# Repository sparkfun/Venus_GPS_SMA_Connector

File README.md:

**NOTE:** *This product has been retired from our catalog. If you are looking for more up-to-date info, please check out some of these resources to see how other users are still hacking and improving on this product.*
* *[SparkFun Forum](https://forum.sparkfun.com/)*
* *[Comments Here on GitHub](https://github.com/sparkfun/Venus_GPS_SMA_Connector/issues)*
* *[IRC Channel](https://www.sparkfun.com/news/263)*

SparkFun Venus GPS with SMA Connector
========================================

[*SparkFun Venus GPS with SMA Connector (GPS-11058)*](https://www.sparkfun.com/products/11058)

This is the latest version of our Venus GPS board; the smallest, most powerful, and most versatile GPS receiver we carry. It’s based on the Venus638FLPx, the successor to the Venus634LPx. 
The Venus638FLPx outputs standard NMEA-0183 or SkyTraq Binary sentences at a default rate of 9600bps (adjustable to 115200bps), with update rates up to 20Hz! 
The Venus638FLPx also allows for limited on-chip logging (check out the firmware below), as well as external logging using a SPI flash memory chip (not included).

Repository Contents
-------------------

* **/Hardware** - Eagle design files (.brd, .sch)
* **/Production** - Production panel files (.brd)

Documentation
--------------

* **[SparkFun Fritzing repo](https://github.com/sparkfun/Fritzing_Parts)** - Fritzing diagrams for SparkFun products.
* **[SparkFun 3D Model repo](https://github.com/sparkfun/3D_Models)** - 3D models of SparkFun products. 

License Information
-------------------
This product is _**open source**_! 

The **hardware** is released under [Creative Commons ShareAlike 4.0 International](https://creativecommons.org/licenses/by-sa/4.0/).

Please use, reuse, and modify these files as you see fit. Please maintain attribution to SparkFun Electronics and release anything derivative under the same license.

Distributed as-is; no warranty is given.

- Your friends at SparkFun.

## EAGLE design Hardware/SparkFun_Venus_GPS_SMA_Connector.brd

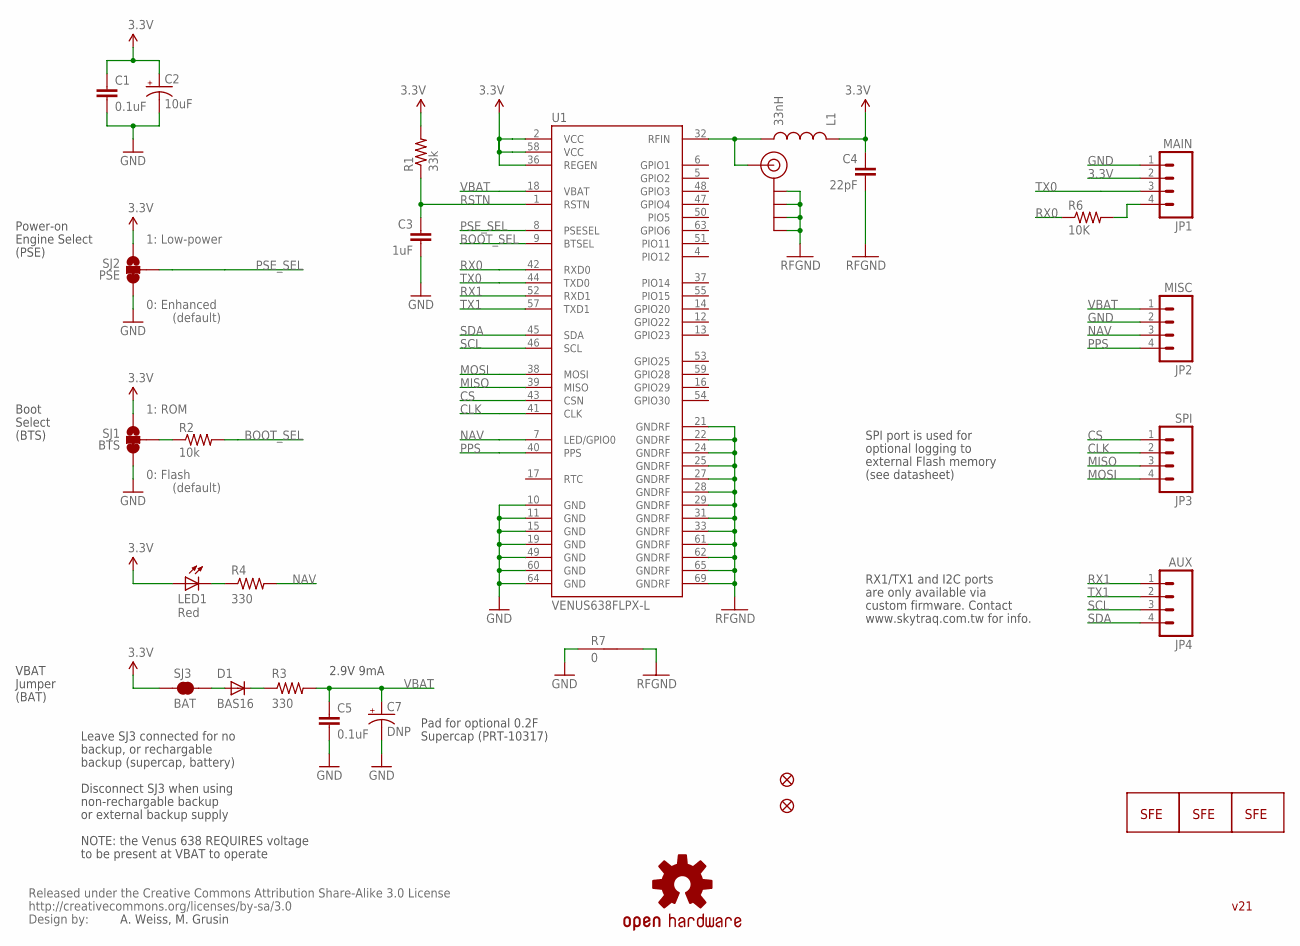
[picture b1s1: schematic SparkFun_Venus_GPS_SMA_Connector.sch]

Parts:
C1, C5: 0.1uF; 0402-CAP
C2: 10uF; EIA3216
C3: 1uF; 0402-CAP
C4: 22pF; 0402-CAP
C7: DNP; EN_J2
D1: BAS16; SOD-323
JP1: MAIN; 1X04
JP2: MISC; 1X04
JP3: SPI; 1X04
JP4: AUX; 1X04
JP5: SMA_EDGE; SMA-EDGE
JP6, JP7: FIDUCIALUFIDUCIAL; MICRO-FIDUCIAL
L1: 33nH; C0402
LED1: Red; LED-0603
LOGO1, LOGO2: LOGO-SFESK; SFE-LOGO-FLAME
LOGO3: LOGO-SFENW2; SFE-NEW-WEB
R1: 33k; 0402-RES
R2: 10k; 0402-RES
R3, R4: 330; 0402-RES
R6: 10K; 0402-RES
R7: 0; GND-JUMP
SJ1: BTS; SJ_3_PASTE2&3
SJ2: PSE; SJ_3_PASTE2&3
SJ3: BAT; SJ_2S
U1: VENUS638FLPX-L; VENUS638FLPX
U$4: OSHW-LOGOS; OSHW-LOGO-S
U$5: CREATIVE_COMMONS

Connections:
3.3V: C1.1, C2.A (+), C4.1, JP1.2, L1.1, LED1.A, R1.2, SJ1.1, SJ2.1, SJ3.1, U1.2 (VCC), U1.36 (REGEN), U1.58 (VCC)
ANT: JP5.SIG (SIGNAL), L1.2, U1.32 (RFIN)
BOOT_SEL: R2.2, U1.9 (BTSEL)
CLK: JP3.2, U1.41 (CLK)
CS: JP3.1, U1.43 (CSN)
GND: C1.2, C2.C (-), C3.2, C5.2, C7.-, JP1.1, JP2.2, R7.1, SJ1.3, SJ2.3, U1.10 (GND), U1.11 (GND), U1.15 (GND), U1.19 (GND), U1.49 (GND), U1.60 (GND), U1.64 (GND)
MISO: JP3.3, U1.39 (MISO)
MOSI: JP3.4, U1.38 (MOSI)
unnamed: LED1.C, R4.1
unnamed: R2.1, SJ1.2
unnamed: D1.1 (C), R3.1
unnamed: D1.2 (A), SJ3.2
NAV: JP2.3, R4.2, U1.7 (LED/GPIO0)
PPS: JP2.4, U1.40 (PPS)
PSE_SEL: SJ2.2, U1.8 (PSESEL)
RFGND: C4.2, JP5.GND@0 (GND), JP5.GND@1 (GND), JP5.GND@2 (GND), JP5.GND@3 (GND), R7.2, U1.21 (GNDRF), U1.22 (GNDRF), U1.24 (GNDRF), U1.25 (GNDRF), U1.27 (GNDRF), U1.28 (GNDRF), U1.29 (GNDRF), U1.31 (GNDRF), U1.33 (GNDRF), U1.61 (GNDRF), U1.62 (GNDRF), U1.65 (GNDRF), U1.69 (GNDRF)
RSTN: C3.1, R1.1, U1.1 (RSTN)
RX0: R6.1, U1.42 (RXD0)
RX1: JP4.1, U1.52 (RXD1)
RX01: JP1.4, R6.2
SCL: JP4.3, U1.46 (SCL)
SDA: JP4.4, U1.45 (SDA)
TX0: JP1.3, U1.44 (TXD0)
TX1: JP4.2, U1.57 (TXD1)
VBAT: C5.1, C7.+, JP2.1, R3.2, U1.18 (VBAT)

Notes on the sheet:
RFGND
1: Low-power
0: Enhanced
0: Flash
1: ROM
(default)
A. Weiss, M. Grusin
Supercap (PRT-10317)
Pad for optional 0.2F
2.9V 9mA
RX1/TX1 and I2C ports
are only available via
SPI port is used for
optional logging to
external Flash memory
(see datasheet)
custom firmware. Contact
www.skytraq.com.tw for info.
Power-on
Engine Select
Boot
Select
(PSE)
(BTS)
VBAT
Jumper
(BAT)
Leave SJ3 connected for no
backup, or rechargable
backup (supercap, battery)
Disconnect SJ3 when using
non-rechargable backup
or external backup supply
NOTE: the Venus 638 REQUIRES voltage
to be present at VBAT to operate
v21

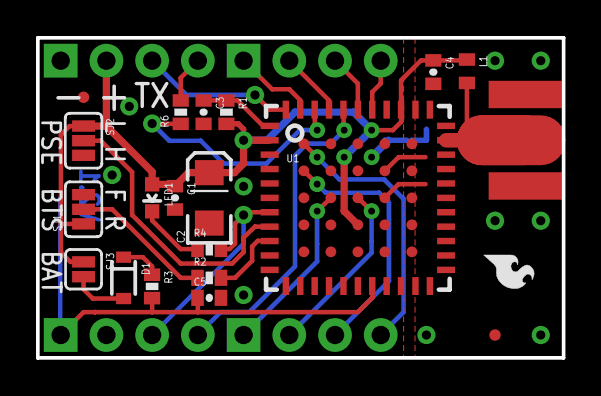
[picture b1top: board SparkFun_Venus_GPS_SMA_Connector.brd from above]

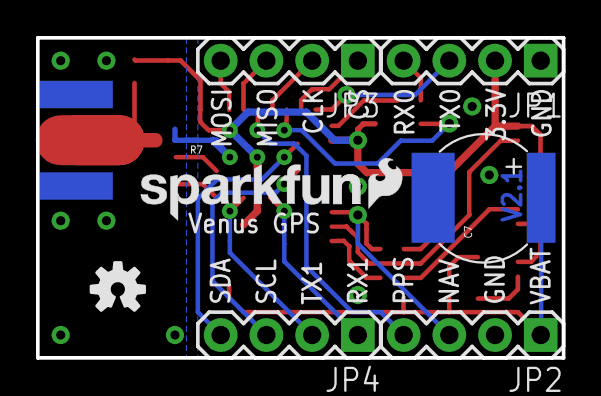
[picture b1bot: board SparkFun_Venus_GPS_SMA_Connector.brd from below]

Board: 2 copper layers, 29.2 x 17.8 mm, 31 parts (9 on the bottom side), 25 nets.

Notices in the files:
parts and their libraries:
SparkFun: Released under the Creative Commons Attribution Share-Alike 3.0 License
SparkFun: http://creativecommons.org/licenses/by-sa/3.0
SparkFun-Aesthetics: Licensing: CC v3.0 Share-Alike You are welcome to use this library for commercial purposes.
